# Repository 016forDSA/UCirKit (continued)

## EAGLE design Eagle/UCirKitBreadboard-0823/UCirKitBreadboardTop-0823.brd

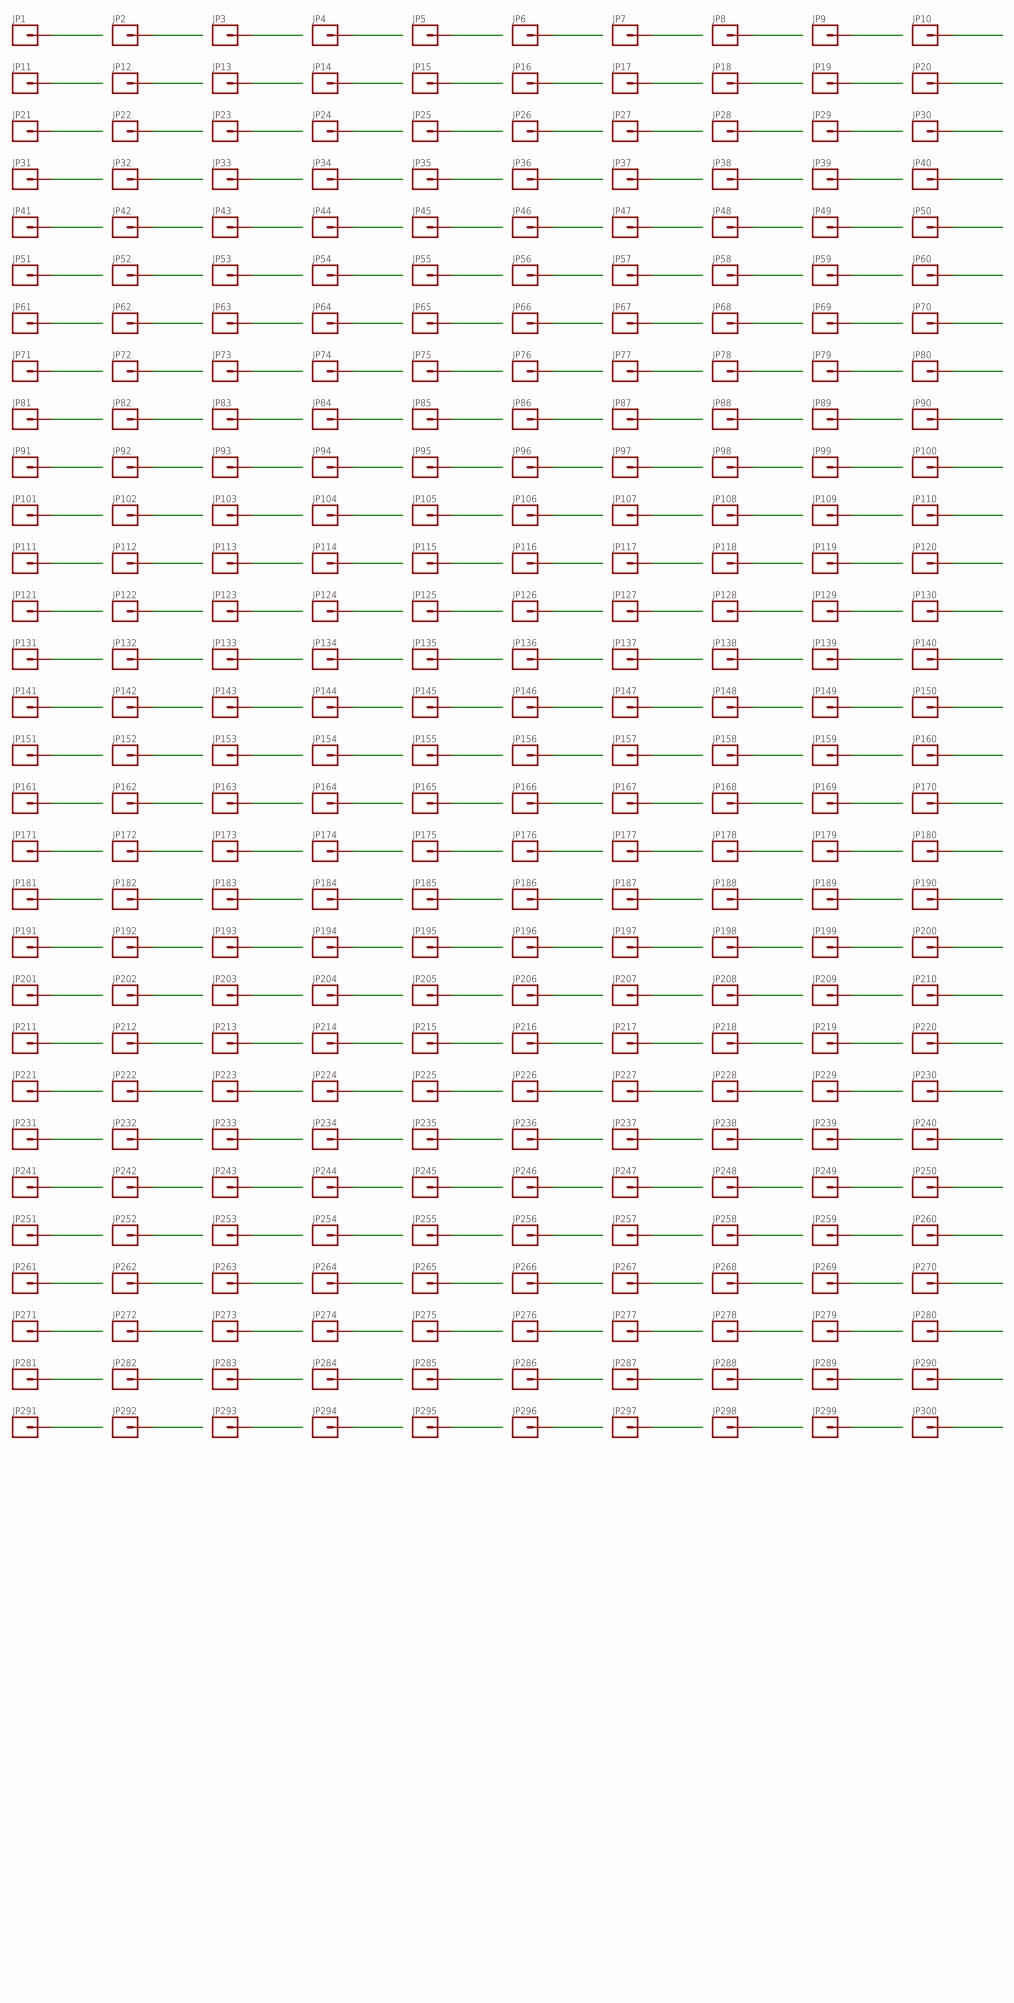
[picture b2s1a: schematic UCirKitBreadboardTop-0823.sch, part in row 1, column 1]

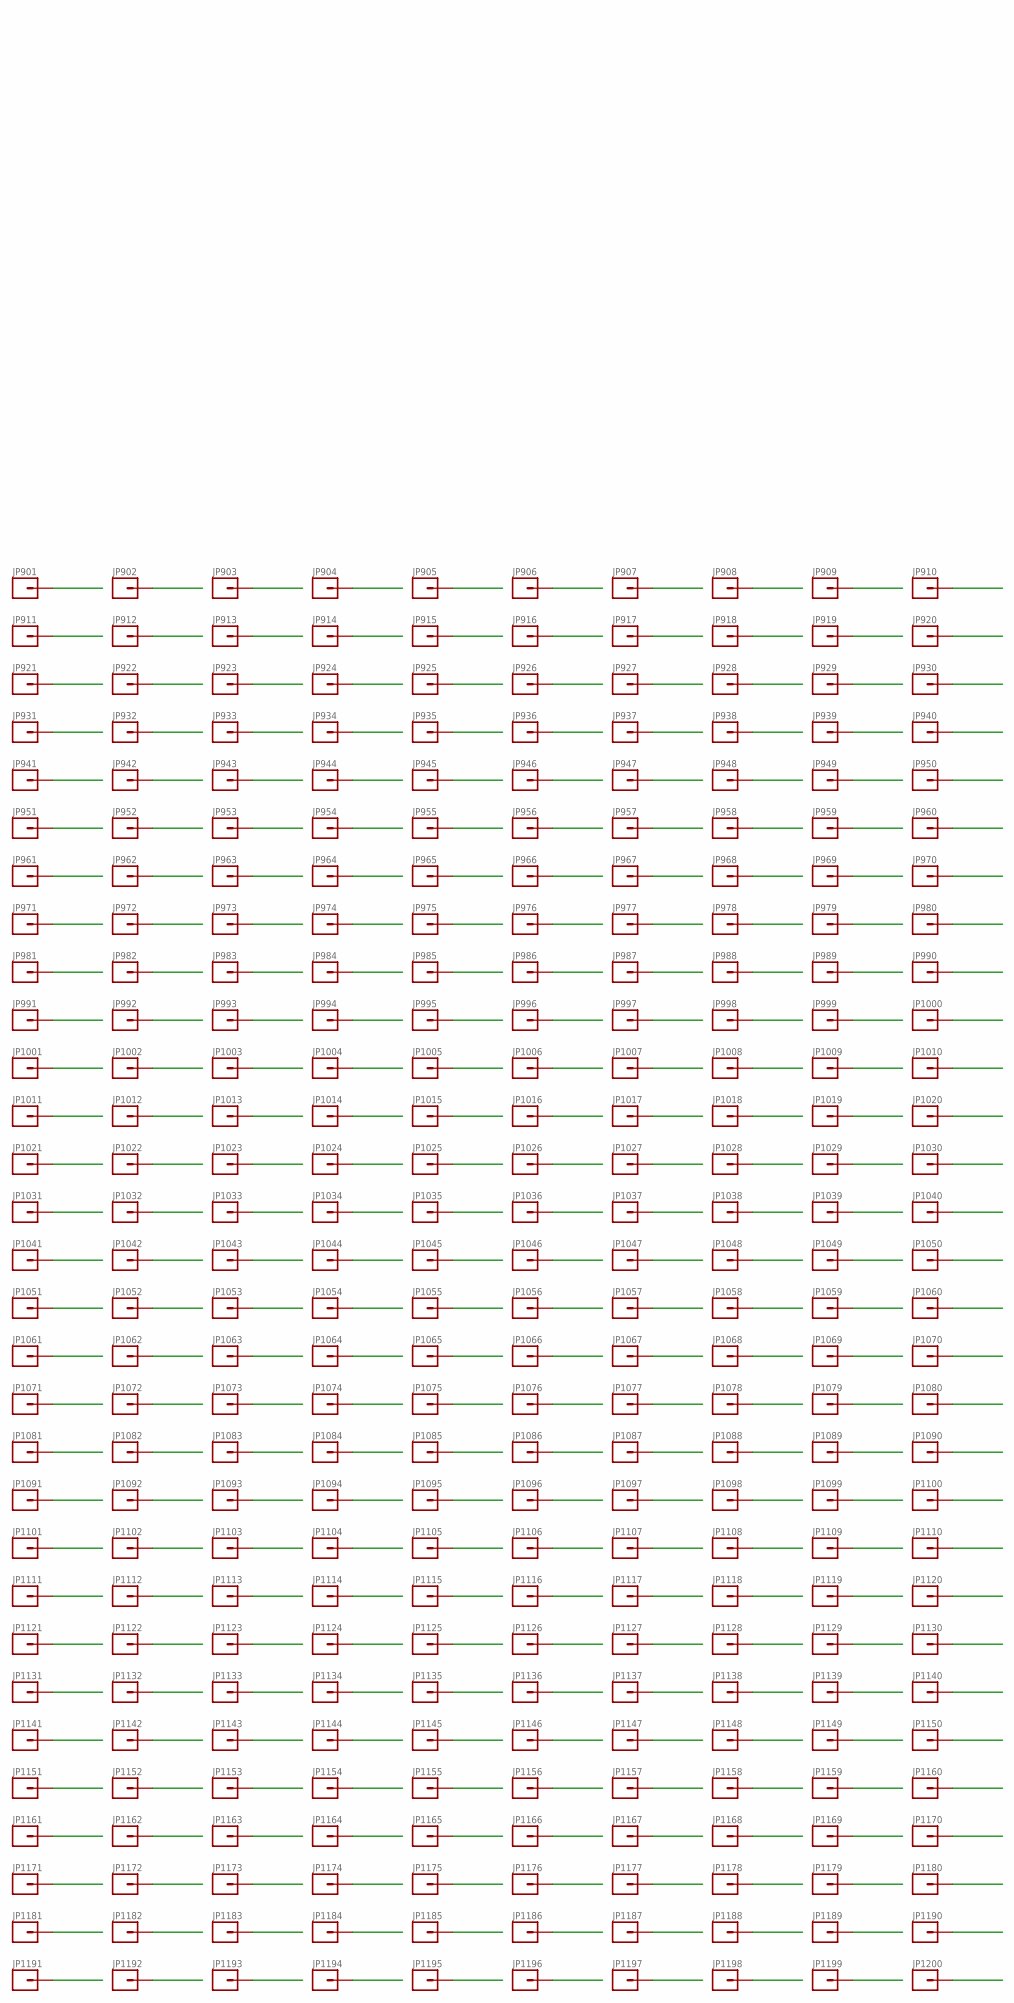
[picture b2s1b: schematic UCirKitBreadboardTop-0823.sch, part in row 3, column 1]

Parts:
JP1, JP2, JP3, JP4, JP5, JP6, JP7, JP8, JP9, JP10, JP11, JP12, JP13, JP14, JP15, JP16, JP17, JP18, JP19, JP20, JP21, JP22, JP23, JP24, JP25, JP26, JP27, JP28, JP29, JP30, JP31, JP32, JP33, JP34, JP35, JP36, JP37, JP38, JP39, JP40, JP41, JP42, JP43, JP44, JP45, JP46, JP47, JP48, JP49, JP50, JP51, JP52, JP53, JP54, JP55, JP56, JP57, JP58, JP59, JP60, JP61, JP62, JP63, JP64, JP65, JP66, JP67, JP68, JP69, JP70, JP71, JP72, JP73, JP74, JP75, JP76, JP77, JP78, JP79, JP80, JP81, JP82, JP83, JP84, JP85, JP86, JP87, JP88, JP89, JP90, JP91, JP92, JP93, JP94, JP95, JP96, JP97, JP98, JP99, JP100, JP101, JP102, JP103, JP104, JP105, JP106, JP107, JP108, JP109, JP110, JP111, JP112, JP113, JP114, JP115, JP116, JP117, JP118, JP119, JP120, JP121, JP122, JP123, JP124, JP125, JP126, JP127, JP128, JP129, JP130, JP131, JP132, JP133, JP134, JP135, JP136, JP137, JP138, JP139, JP140, JP141, JP142, JP143, JP144, JP145, JP146, JP147, JP148, JP149, JP150, JP151, JP152, JP153, JP154, JP155, JP156, JP157, JP158, JP159, JP160, JP161, JP162, JP163, JP164, JP165, JP166, JP167, JP168, JP169, JP170, JP171, JP172, JP173, JP174, JP175, JP176, JP177, JP178, JP179, JP180, JP181, JP182, JP183, JP184, JP185, JP186, JP187, JP188, JP189, JP190, JP191, JP192, JP193, JP194, JP195, JP196, JP197, JP198, JP199, JP200, JP201, JP202, JP203, JP204, JP205, JP206, JP207, JP208, JP209, JP210, JP211, JP212, JP213, JP214, JP215, JP216, JP217, JP218, JP219, JP220, JP221, JP222, JP223, JP224, JP225, JP226, JP227, JP228, JP229, JP230, JP231, JP232, JP233, JP234, JP235, JP236, JP237, JP238, JP239, JP240, JP241, JP242, JP243, JP244, JP245, JP246, JP247, JP248, JP249, JP250, JP251, JP252, JP253, JP254, JP255, JP256, JP257, JP258, JP259, JP260, JP261, JP262, JP263, JP264, JP265, JP266, JP267, JP268, JP269, JP270, JP271, JP272, JP273, JP274, JP275, JP276, JP277, JP278, JP279, JP280, JP281, JP282, JP283, JP284, JP285, JP286, JP287, JP288, JP289, JP290, JP291, JP292, JP293, JP294, JP295, JP296, JP297, JP298, JP299, JP300: M01PTH_WITHOUT_TEXT; 1X01_WITHOUT_TEXT
JP901, JP902, JP903, JP904, JP905, JP906, JP907, JP908, JP909, JP910, JP911, JP912, JP913, JP914, JP915, JP916, JP917, JP918, JP919, JP920, JP921, JP922, JP923, JP924, JP925, JP926, JP927, JP928, JP929, JP930, JP931, JP932, JP933, JP934, JP935, JP936, JP937, JP938, JP939, JP940, JP941, JP942, JP943, JP944, JP945, JP946, JP947, JP948, JP949, JP950, JP951, JP952, JP953, JP954, JP955, JP956, JP957, JP958, JP959, JP960, JP961, JP962, JP963, JP964, JP965, JP966, JP967, JP968, JP969, JP970, JP971, JP972, JP973, JP974, JP975, JP976, JP977, JP978, JP979, JP980, JP981, JP982, JP983, JP984, JP985, JP986, JP987, JP988, JP989, JP990, JP991, JP992, JP993, JP994, JP995, JP996, JP997, JP998, JP999, JP1000, JP1001, JP1002, JP1003, JP1004, JP1005, JP1006, JP1007, JP1008, JP1009, JP1010, JP1011, JP1012, JP1013, JP1014, JP1015, JP1016, JP1017, JP1018, JP1019, JP1020, JP1021, JP1022, JP1023, JP1024, JP1025, JP1026, JP1027, JP1028, JP1029, JP1030, JP1031, JP1032, JP1033, JP1034, JP1035, JP1036, JP1037, JP1038, JP1039, JP1040, JP1041, JP1042, JP1043, JP1044, JP1045, JP1046, JP1047, JP1048, JP1049, JP1050, JP1051, JP1052, JP1053, JP1054, JP1055, JP1056, JP1057, JP1058, JP1059, JP1060, JP1061, JP1062, JP1063, JP1064, JP1065, JP1066, JP1067, JP1068, JP1069, JP1070, JP1071, JP1072, JP1073, JP1074, JP1075, JP1076, JP1077, JP1078, JP1079, JP1080, JP1081, JP1082, JP1083, JP1084, JP1085, JP1086, JP1087, JP1088, JP1089, JP1090, JP1091, JP1092, JP1093, JP1094, JP1095, JP1096, JP1097, JP1098, JP1099, JP1100, JP1101, JP1102, JP1103, JP1104, JP1105, JP1106, JP1107, JP1108, JP1109, JP1110, JP1111, JP1112, JP1113, JP1114, JP1115, JP1116, JP1117, JP1118, JP1119, JP1120, JP1121, JP1122, JP1123, JP1124, JP1125, JP1126, JP1127, JP1128, JP1129, JP1130, JP1131, JP1132, JP1133, JP1134, JP1135, JP1136, JP1137, JP1138, JP1139, JP1140, JP1141, JP1142, JP1143, JP1144, JP1145, JP1146, JP1147, JP1148, JP1149, JP1150, JP1151, JP1152, JP1153, JP1154, JP1155, JP1156, JP1157, JP1158, JP1159, JP1160, JP1161, JP1162, JP1163, JP1164, JP1165, JP1166, JP1167, JP1168, JP1169, JP1170, JP1171, JP1172, JP1173, JP1174, JP1175, JP1176, JP1177, JP1178, JP1179, JP1180, JP1181, JP1182, JP1183, JP1184, JP1185, JP1186, JP1187, JP1188, JP1189, JP1190, JP1191, JP1192, JP1193, JP1194, JP1195, JP1196, JP1197, JP1198, JP1199, JP1200: M01PTH_SMD_3.25X0.85MM_NO_SILK; 1X01_SMD_3.25X0.85MM_NO_SILK

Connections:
0_1440304149: JP1.1, JP961.P$1
0_1440304208: JP5.1, JP1159.P$1
1_1440304149: JP11.1, JP963.P$1
1_1440304208: JP15.1, JP1160.P$1
2_1440304149: JP21.1, JP965.P$1
2_1440304208: JP6.1, JP1171.P$1
3_1440304149: JP31.1, JP967.P$1
3_1440304208: JP16.1, JP1172.P$1
4_1440304149: JP41.1, JP969.P$1
4_1440304208: JP26.1, JP1173.P$1
5_1440304149: JP51.1, JP971.P$1
5_1440304208: JP36.1, JP1174.P$1
6_1440304149: JP61.1, JP973.P$1
6_1440304208: JP46.1, JP1175.P$1
7_1440304149: JP71.1, JP975.P$1
7_1440304208: JP56.1, JP1176.P$1
8_1440304149: JP81.1, JP977.P$1
8_1440304208: JP295.1, JP1189.P$1
9_1440304149: JP91.1, JP979.P$1
9_1440304208: JP285.1, JP1190.P$1
10_1440304149: JP101.1, JP981.P$1
10_1440304208: JP296.1, JP1191.P$1
11_1440304149: JP111.1, JP983.P$1
11_1440304208: JP286.1, JP1192.P$1
12_1440304149: JP121.1, JP985.P$1
12_1440304208: JP276.1, JP1193.P$1
13_1440304149: JP131.1, JP987.P$1
13_1440304208: JP266.1, JP1194.P$1
14_1440304149: JP141.1, JP989.P$1
14_1440304208: JP256.1, JP1195.P$1
15_1440304149: JP151.1, JP991.P$1
15_1440304208: JP25.1, JP1158.P$1
16_1440304149: JP161.1, JP993.P$1
16_1440304208: JP66.1, JP1177.P$1
17_1440304149: JP171.1, JP995.P$1
17_1440304208: JP275.1, JP1188.P$1
18_1440304149: JP181.1, JP997.P$1
18_1440304208: JP246.1, JP1196.P$1
19_1440304149: JP191.1, JP999.P$1
19_1440304208: JP35.1, JP1157.P$1
20_1440304149: JP201.1, JP1001.P$1
20_1440304208: JP265.1, JP1187.P$1
21_1440304149: JP211.1, JP1003.P$1
21_1440304208: JP236.1, JP1197.P$1
22_1440304149: JP221.1, JP1005.P$1
22_1440304208: JP45.1, JP1156.P$1
23_1440304149: JP231.1, JP1007.P$1
23_1440304208: JP76.1, JP1178.P$1
24_1440304149: JP241.1, JP1009.P$1
24_1440304208: JP255.1, JP1186.P$1
25_1440304149: JP251.1, JP1011.P$1
25_1440304208: JP226.1, JP1198.P$1
26_1440304149: JP261.1, JP1013.P$1
26_1440304208: JP55.1, JP1155.P$1
27_1440304149: JP271.1, JP1015.P$1
27_1440304208: JP86.1, JP1179.P$1
28_1440304149: JP281.1, JP1017.P$1
28_1440304208: JP245.1, JP1185.P$1
29_1440304149: JP291.1, JP1019.P$1
29_1440304208: JP216.1, JP1199.P$1
30_1440304149: JP292.1, JP1020.P$1
30_1440304208: JP65.1, JP1154.P$1
31_1440304149: JP10.1, JP1021.P$1
31_1440304208: JP96.1, JP1180.P$1
32_1440304149: JP20.1, JP1023.P$1
32_1440304208: JP235.1, JP1184.P$1
33_1440304149: JP30.1, JP1025.P$1
33_1440304208: JP206.1, JP1200.P$1
34_1440304149: JP40.1, JP1027.P$1
34_1440304208: JP75.1, JP1153.P$1
35_1440304149: JP50.1, JP1029.P$1
35_1440304208: JP225.1, JP1183.P$1
36_1440304149: JP60.1, JP1031.P$1
36_1440304208: JP85.1, JP1152.P$1
37_1440304149: JP70.1, JP1033.P$1
37_1440304208: JP215.1, JP1182.P$1
38_1440304149: JP80.1, JP1035.P$1
38_1440304208: JP95.1, JP1151.P$1
39_1440304149: JP90.1, JP1037.P$1
39_1440304208: JP106.1, JP1161.P$1
40_1440304149: JP100.1, JP1039.P$1
40_1440304208: JP205.1, JP1181.P$1
41_1440304149: JP110.1, JP1041.P$1
41_1440304208: JP105.1, JP1149.P$1
42_1440304149: JP120.1, JP1043.P$1
42_1440304208: JP115.1, JP1150.P$1
43_1440304149: JP130.1, JP1045.P$1
43_1440304208: JP116.1, JP1162.P$1
44_1440304149: JP140.1, JP1047.P$1
44_1440304208: JP126.1, JP1163.P$1
45_1440304149: JP150.1, JP1049.P$1
45_1440304208: JP125.1, JP1148.P$1
46_1440304149: JP160.1, JP1051.P$1
46_1440304208: JP136.1, JP1164.P$1
47_1440304149: JP170.1, JP1053.P$1
47_1440304208: JP135.1, JP1147.P$1
48_1440304149: JP180.1, JP1055.P$1
48_1440304208: JP146.1, JP1165.P$1
49_1440304149: JP190.1, JP1057.P$1
49_1440304208: JP145.1, JP1146.P$1
50_1440304149: JP200.1, JP1059.P$1
50_1440304208: JP156.1, JP1166.P$1
51_1440304149: JP210.1, JP1061.P$1
51_1440304208: JP166.1, JP1167.P$1
52_1440304149: JP220.1, JP1063.P$1
52_1440304208: JP155.1, JP1145.P$1
53_1440304149: JP230.1, JP1065.P$1
53_1440304208: JP176.1, JP1168.P$1
54_1440304149: JP240.1, JP1067.P$1
54_1440304208: JP165.1, JP1144.P$1
55_1440304149: JP250.1, JP1069.P$1
55_1440304208: JP186.1, JP1169.P$1
56_1440304149: JP260.1, JP1071.P$1
56_1440304208: JP175.1, JP1143.P$1
57_1440304149: JP270.1, JP1073.P$1
57_1440304208: JP196.1, JP1170.P$1
58_1440304149: JP280.1, JP1075.P$1
58_1440304208: JP185.1, JP1142.P$1
59_1440304149: JP290.1, JP1077.P$1
59_1440304208: JP195.1, JP1141.P$1
60_1440304149: JP300.1, JP1079.P$1
61_1440304149: JP299.1, JP1080.P$1
62_1440304149: JP2.1, JP962.P$1
63_1440304149: JP12.1, JP964.P$1
64_1440304149: JP22.1, JP966.P$1
65_1440304149: JP32.1, JP968.P$1
66_1440304149: JP42.1, JP970.P$1
67_1440304149: JP52.1, JP972.P$1
68_1440304149: JP62.1, JP974.P$1
69_1440304149: JP72.1, JP976.P$1
70_1440304149: JP82.1, JP978.P$1
71_1440304149: JP92.1, JP980.P$1
72_1440304149: JP102.1, JP982.P$1
73_1440304149: JP112.1, JP984.P$1
74_1440304149: JP122.1, JP986.P$1
75_1440304149: JP132.1, JP988.P$1
76_1440304149: JP142.1, JP990.P$1
77_1440304149: JP152.1, JP992.P$1
78_1440304149: JP162.1, JP994.P$1
79_1440304149: JP172.1, JP996.P$1
80_1440304149: JP182.1, JP998.P$1
81_1440304149: JP192.1, JP1000.P$1
82_1440304149: JP202.1, JP1002.P$1
83_1440304149: JP212.1, JP1004.P$1
84_1440304149: JP222.1, JP1006.P$1
85_1440304149: JP232.1, JP1008.P$1
86_1440304149: JP242.1, JP1010.P$1
87_1440304149: JP252.1, JP1012.P$1
88_1440304149: JP262.1, JP1014.P$1
89_1440304149: JP272.1, JP1016.P$1
90_1440304149: JP282.1, JP1018.P$1
91_1440304149: JP9.1, JP1022.P$1
92_1440304149: JP19.1, JP1024.P$1
93_1440304149: JP29.1, JP1026.P$1
94_1440304149: JP39.1, JP1028.P$1
95_1440304149: JP49.1, JP1030.P$1
96_1440304149: JP59.1, JP1032.P$1
97_1440304149: JP69.1, JP1034.P$1
98_1440304149: JP79.1, JP1036.P$1
99_1440304149: JP89.1, JP1038.P$1
100_1440304149: JP99.1, JP1040.P$1
101_1440304149: JP109.1, JP1042.P$1
102_1440304149: JP119.1, JP1044.P$1
103_1440304149: JP129.1, JP1046.P$1
104_1440304149: JP139.1, JP1048.P$1
105_1440304149: JP149.1, JP1050.P$1
106_1440304149: JP159.1, JP1052.P$1
107_1440304149: JP169.1, JP1054.P$1
108_1440304149: JP179.1, JP1056.P$1
109_1440304149: JP189.1, JP1058.P$1
110_1440304149: JP199.1, JP1060.P$1
111_1440304149: JP209.1, JP1062.P$1
112_1440304149: JP219.1, JP1064.P$1
113_1440304149: JP229.1, JP1066.P$1
114_1440304149: JP239.1, JP1068.P$1
115_1440304149: JP249.1, JP1070.P$1
116_1440304149: JP259.1, JP1072.P$1
117_1440304149: JP269.1, JP1074.P$1
118_1440304149: JP279.1, JP1076.P$1
119_1440304149: JP289.1, JP1078.P$1
120_1440304149: JP8.1, JP1081.P$1
121_1440304149: JP18.1, JP1083.P$1
122_1440304149: JP28.1, JP1085.P$1
123_1440304149: JP38.1, JP1087.P$1
124_1440304149: JP48.1, JP1089.P$1
125_1440304149: JP58.1, JP1091.P$1
126_1440304149: JP68.1, JP1093.P$1
127_1440304149: JP78.1, JP1095.P$1
128_1440304149: JP88.1, JP1097.P$1
129_1440304149: JP98.1, JP1099.P$1
130_1440304149: JP108.1, JP1101.P$1
131_1440304149: JP118.1, JP1103.P$1
132_1440304149: JP128.1, JP1105.P$1
133_1440304149: JP138.1, JP1107.P$1
134_1440304149: JP148.1, JP1109.P$1
135_1440304149: JP158.1, JP1111.P$1
136_1440304149: JP168.1, JP1113.P$1
137_1440304149: JP178.1, JP1115.P$1
138_1440304149: JP188.1, JP1117.P$1
139_1440304149: JP198.1, JP1119.P$1
140_1440304149: JP208.1, JP1121.P$1
141_1440304149: JP218.1, JP1123.P$1
142_1440304149: JP228.1, JP1125.P$1
143_1440304149: JP238.1, JP1127.P$1
144_1440304149: JP248.1, JP1129.P$1
145_1440304149: JP258.1, JP1131.P$1
146_1440304149: JP268.1, JP1133.P$1
147_1440304149: JP278.1, JP1135.P$1
148_1440304149: JP288.1, JP1137.P$1
149_1440304149: JP298.1, JP1139.P$1
150_1440304149: JP297.1, JP1140.P$1
151_1440304149: JP3.1, JP901.P$1
152_1440304149: JP13.1, JP903.P$1
153_1440304149: JP23.1, JP905.P$1
154_1440304149: JP33.1, JP907.P$1
155_1440304149: JP43.1, JP909.P$1
156_1440304149: JP53.1, JP911.P$1
157_1440304149: JP63.1, JP913.P$1
158_1440304149: JP73.1, JP915.P$1
159_1440304149: JP83.1, JP917.P$1
160_1440304149: JP93.1, JP919.P$1
161_1440304149: JP103.1, JP921.P$1
162_1440304149: JP113.1, JP923.P$1
163_1440304149: JP123.1, JP925.P$1
164_1440304149: JP133.1, JP927.P$1
165_1440304149: JP143.1, JP929.P$1
166_1440304149: JP153.1, JP931.P$1
167_1440304149: JP163.1, JP933.P$1
168_1440304149: JP173.1, JP935.P$1
169_1440304149: JP183.1, JP937.P$1
170_1440304149: JP193.1, JP939.P$1
171_1440304149: JP203.1, JP941.P$1
172_1440304149: JP213.1, JP943.P$1
173_1440304149: JP223.1, JP945.P$1
174_1440304149: JP233.1, JP947.P$1
175_1440304149: JP243.1, JP949.P$1
176_1440304149: JP253.1, JP951.P$1
177_1440304149: JP263.1, JP953.P$1
178_1440304149: JP273.1, JP955.P$1
179_1440304149: JP283.1, JP957.P$1
180_1440304149: JP293.1, JP959.P$1
181_1440304149: JP294.1, JP960.P$1
182_1440304149: JP7.1, JP1082.P$1
183_1440304149: JP17.1, JP1084.P$1
184_1440304149: JP27.1, JP1086.P$1
185_1440304149: JP37.1, JP1088.P$1
186_1440304149: JP47.1, JP1090.P$1
187_1440304149: JP57.1, JP1092.P$1
188_1440304149: JP67.1, JP1094.P$1
189_1440304149: JP77.1, JP1096.P$1
190_1440304149: JP87.1, JP1098.P$1
191_1440304149: JP97.1, JP1100.P$1
192_1440304149: JP107.1, JP1102.P$1
193_1440304149: JP117.1, JP1104.P$1
194_1440304149: JP127.1, JP1106.P$1
195_1440304149: JP137.1, JP1108.P$1
196_1440304149: JP147.1, JP1110.P$1
197_1440304149: JP157.1, JP1112.P$1
198_1440304149: JP167.1, JP1114.P$1
199_1440304149: JP177.1, JP1116.P$1
200_1440304149: JP187.1, JP1118.P$1
201_1440304149: JP197.1, JP1120.P$1
202_1440304149: JP207.1, JP1122.P$1
203_1440304149: JP217.1, JP1124.P$1
204_1440304149: JP227.1, JP1126.P$1
205_1440304149: JP237.1, JP1128.P$1
206_1440304149: JP247.1, JP1130.P$1
207_1440304149: JP257.1, JP1132.P$1
208_1440304149: JP267.1, JP1134.P$1
209_1440304149: JP277.1, JP1136.P$1
210_1440304149: JP287.1, JP1138.P$1
211_1440304149: JP4.1, JP902.P$1
212_1440304149: JP14.1, JP904.P$1
213_1440304149: JP24.1, JP906.P$1
214_1440304149: JP34.1, JP908.P$1
215_1440304149: JP44.1, JP910.P$1
216_1440304149: JP54.1, JP912.P$1
217_1440304149: JP64.1, JP914.P$1
218_1440304149: JP74.1, JP916.P$1
219_1440304149: JP84.1, JP918.P$1
220_1440304149: JP94.1, JP920.P$1
221_1440304149: JP104.1, JP922.P$1
222_1440304149: JP114.1, JP924.P$1
223_1440304149: JP124.1, JP926.P$1
224_1440304149: JP134.1, JP928.P$1
225_1440304149: JP144.1, JP930.P$1
226_1440304149: JP154.1, JP932.P$1
227_1440304149: JP164.1, JP934.P$1
228_1440304149: JP174.1, JP936.P$1
229_1440304149: JP184.1, JP938.P$1
230_1440304149: JP194.1, JP940.P$1
231_1440304149: JP204.1, JP942.P$1
232_1440304149: JP214.1, JP944.P$1
233_1440304149: JP224.1, JP946.P$1
234_1440304149: JP234.1, JP948.P$1
235_1440304149: JP244.1, JP950.P$1
236_1440304149: JP254.1, JP952.P$1
237_1440304149: JP264.1, JP954.P$1
238_1440304149: JP274.1, JP956.P$1
239_1440304149: JP284.1, JP958.P$1

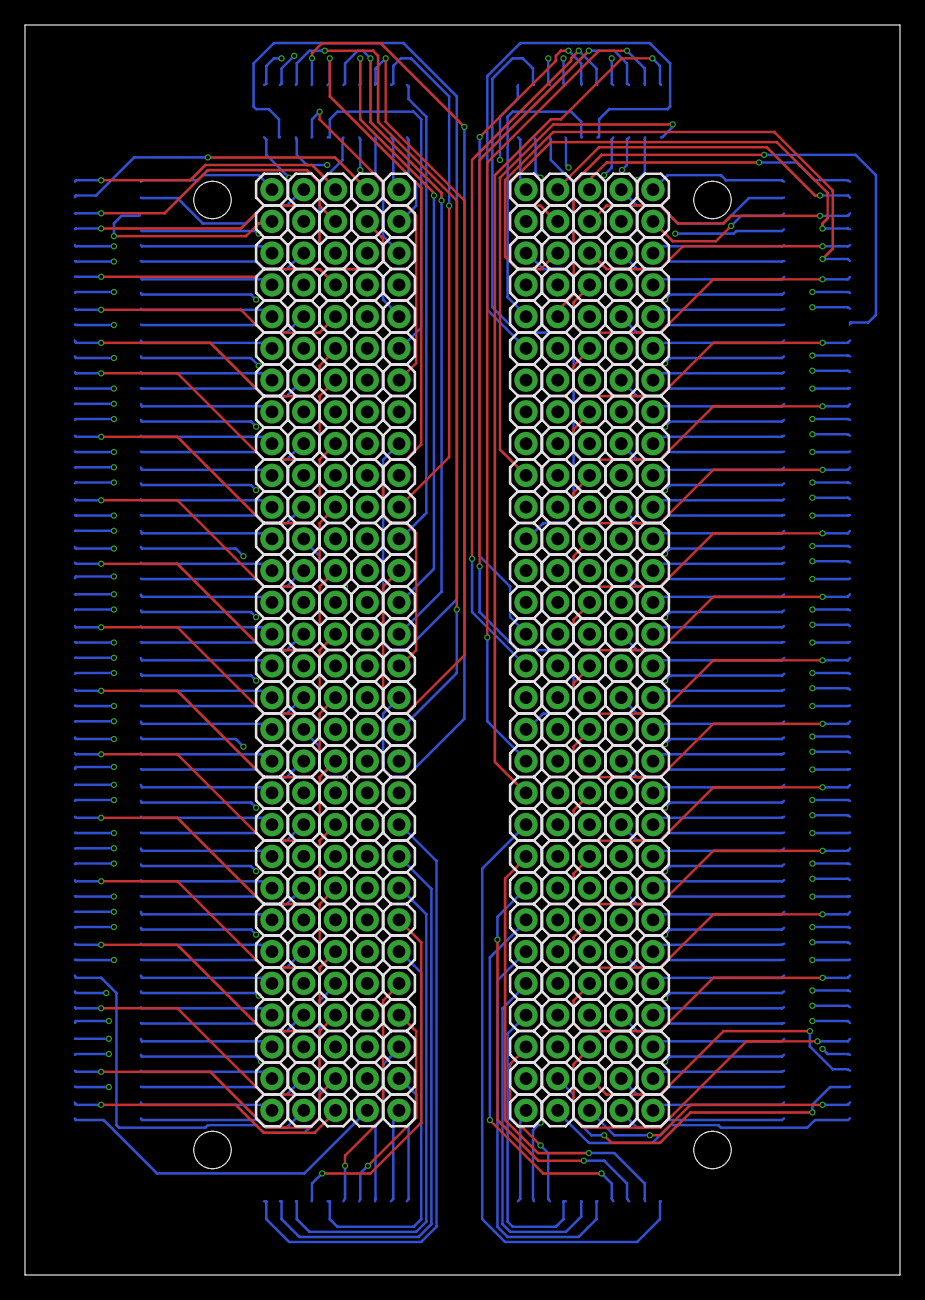
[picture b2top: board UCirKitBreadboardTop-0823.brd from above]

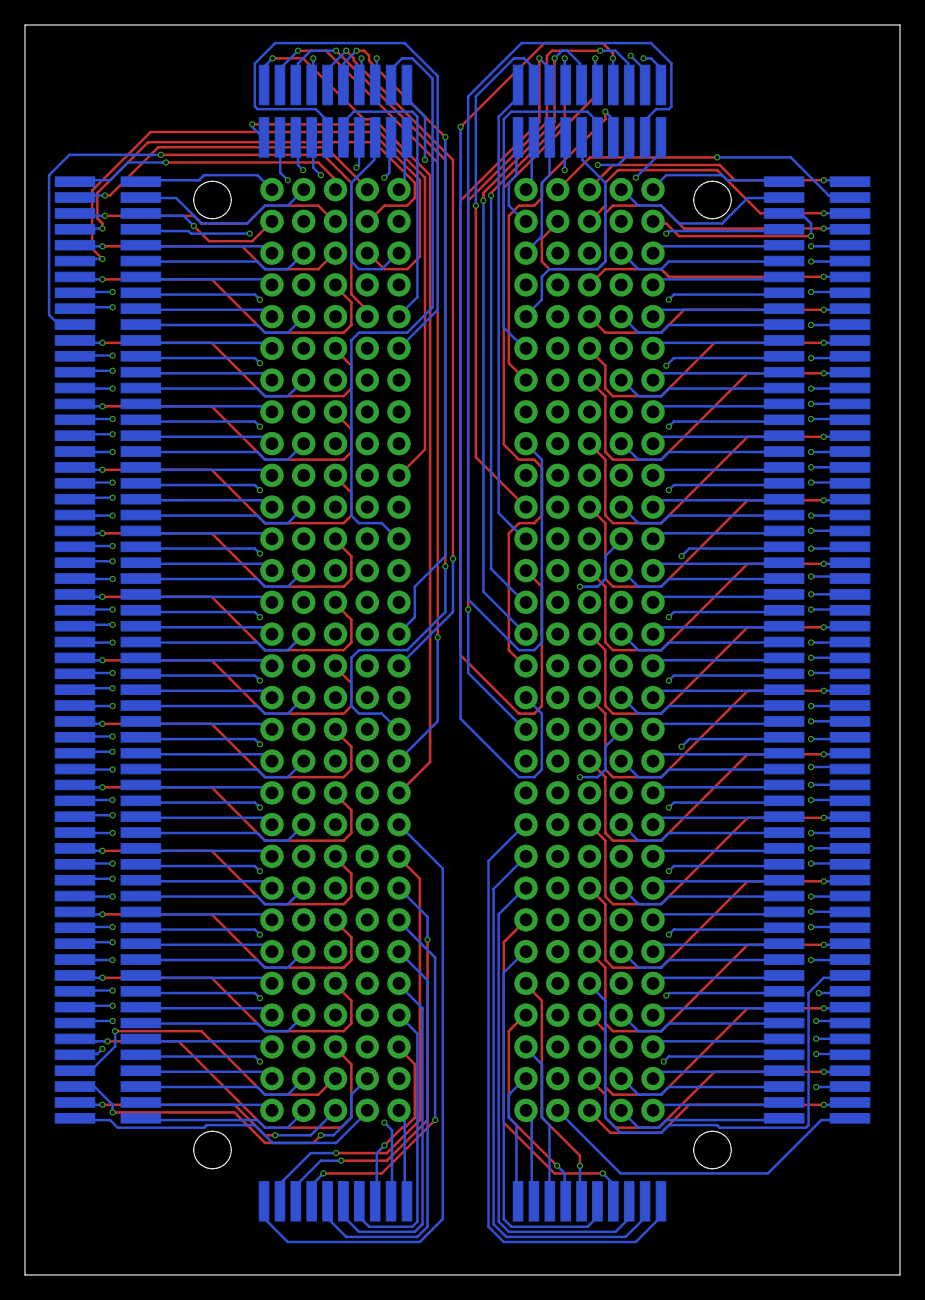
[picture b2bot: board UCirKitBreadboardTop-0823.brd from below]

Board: 4 copper layers, 70.0 x 100.0 mm, 600 parts (300 on the bottom side), 300 nets.

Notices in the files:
parts and their libraries:
SparkFun-Connectors: Licensing: Creative Commons ShareAlike 4.0 International - https://creativecommons.org/licenses/by-sa/4.0
